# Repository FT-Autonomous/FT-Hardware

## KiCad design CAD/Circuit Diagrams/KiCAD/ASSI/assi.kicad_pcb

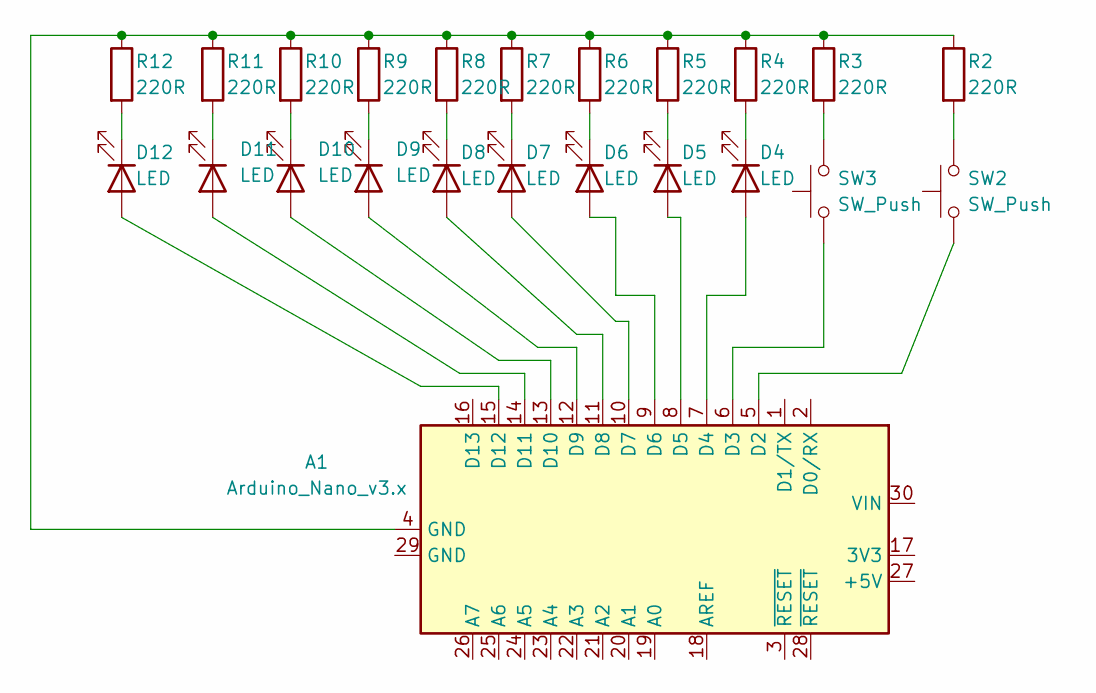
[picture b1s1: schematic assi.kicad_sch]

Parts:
A1: Arduino_Nano_v3.x; Arduino_Nano
D4, D5, D6, D7, D8, D9, D10, D11, D12: LED; LED_D5.0mm
R2, R3, R4, R5, R6, R7, R8, R9, R10, R11, R12: 220R; R_Axial_DIN0207_L6.3mm_D2.5mm_P7.62mm_Horizontal
SW2, SW3: SW_Push; SW_PUSH_6mm

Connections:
unnamed: A1.4 (GND), R2.1, R3.1, R4.1, R5.1, R6.1, R7.1, R8.1, R9.1, R10.1, R11.1, R12.1
unnamed: A1.5 (D2), SW2.1
unnamed: A1.6 (D3), SW3.1
unnamed: A1.7 (D4), D4.2 (A)
unnamed: A1.8 (D5), D5.2 (A)
unnamed: A1.9 (D6), D6.2 (A)
unnamed: A1.10 (D7), D7.2 (A)
unnamed: A1.11 (D8), D8.2 (A)
unnamed: A1.12 (D9), D9.2 (A)
unnamed: A1.13 (D10), D10.2 (A)
unnamed: A1.14 (D11), D11.2 (A)
unnamed: A1.15 (D12), D12.2 (A)
unnamed: D4.1 (K), R4.2
unnamed: D5.1 (K), R5.2
unnamed: D6.1 (K), R6.2
unnamed: D7.1 (K), R7.2
unnamed: D8.1 (K), R8.2
unnamed: D9.1 (K), R9.2
unnamed: D10.1 (K), R10.2
unnamed: D11.1 (K), R11.2
unnamed: D12.1 (K), R12.2
unnamed: R2.2, SW2.2
unnamed: R3.2, SW3.2

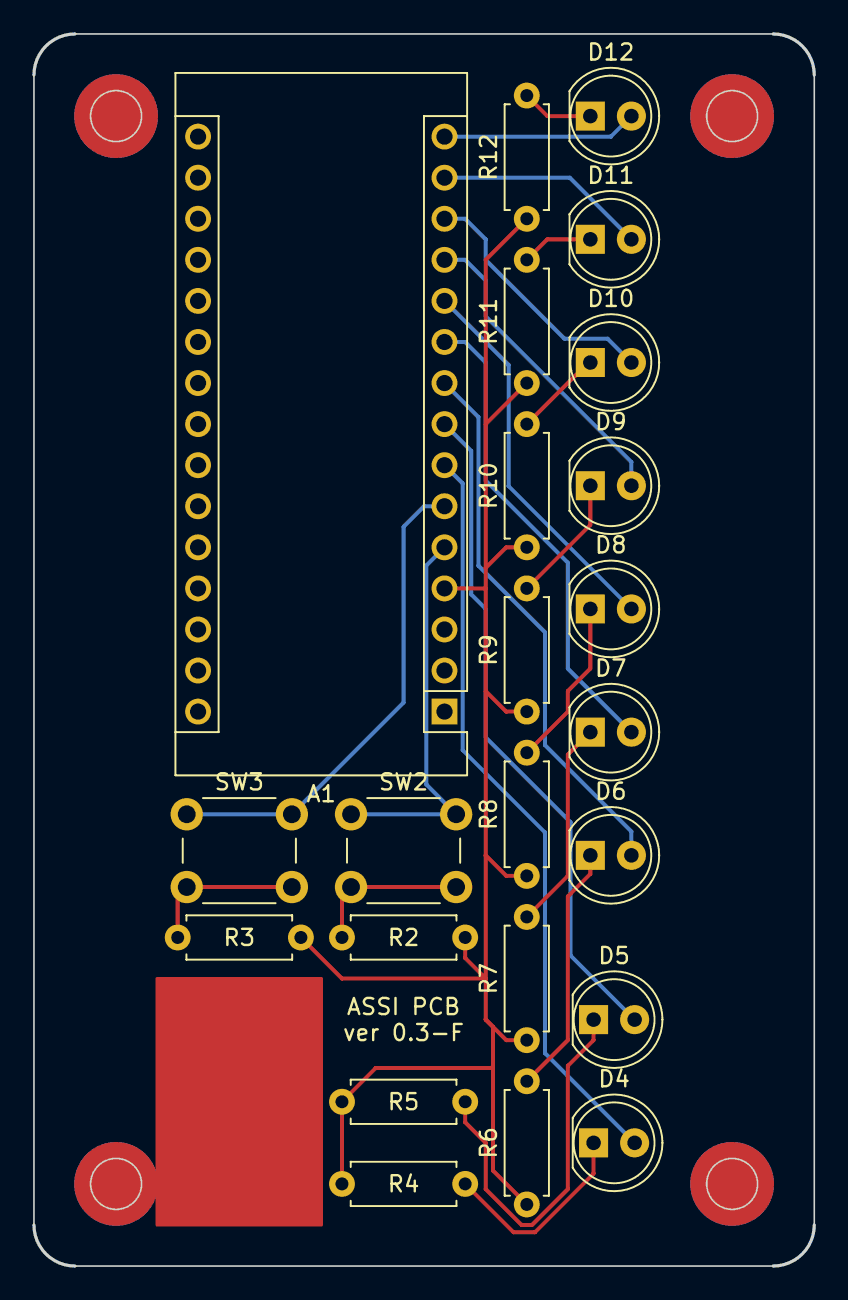
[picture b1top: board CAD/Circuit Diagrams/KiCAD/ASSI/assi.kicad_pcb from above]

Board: 2 copper layers, 48.3 x 76.2 mm, 23 parts (0 on the bottom side), 23 nets.

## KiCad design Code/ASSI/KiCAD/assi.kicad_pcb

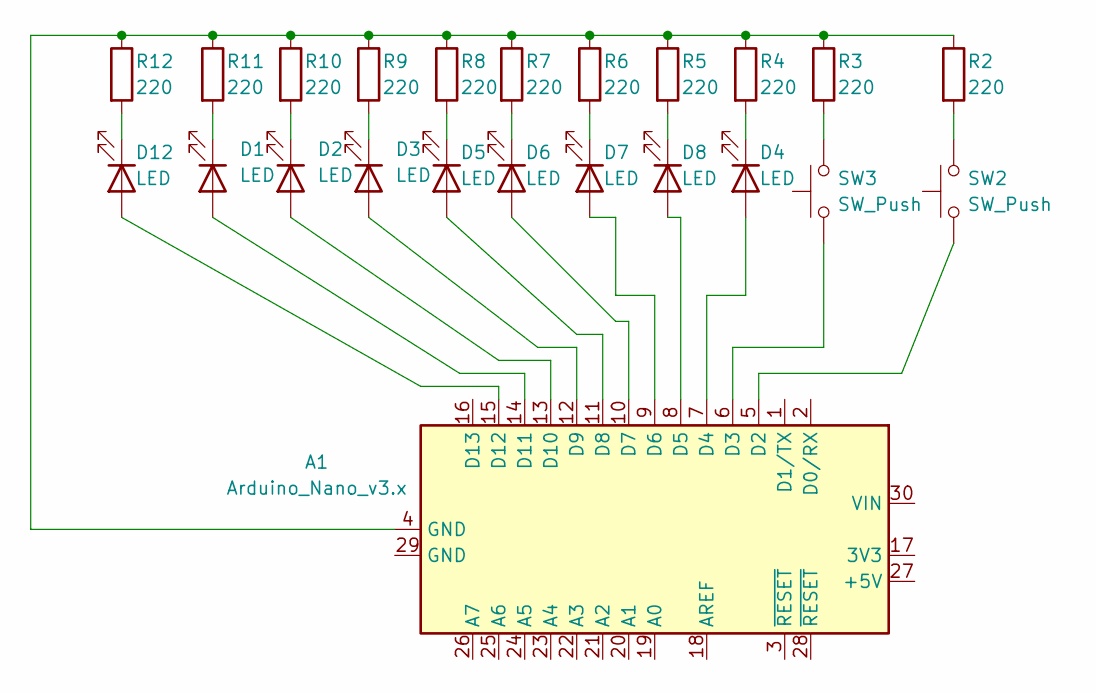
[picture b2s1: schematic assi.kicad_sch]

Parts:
A1: Arduino_Nano_v3.x; Arduino_Nano
D1, D2, D3, D4, D5, D6, D7, D8, D12: LED; LED_D5.0mm
R2, R3, R4, R5, R6, R7, R8, R9, R10, R11, R12: 220; R_Axial_DIN0207_L6.3mm_D2.5mm_P7.62mm_Horizontal
SW2, SW3: SW_Push; SW_PUSH_6mm

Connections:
unnamed: A1.4 (GND), R2.1, R3.1, R4.1, R5.1, R6.1, R7.1, R8.1, R9.1, R10.1, R11.1, R12.1
unnamed: A1.5 (D2), SW2.1
unnamed: A1.6 (D3), SW3.1
unnamed: A1.7 (D4), D4.2 (A)
unnamed: A1.8 (D5), D8.2 (A)
unnamed: A1.9 (D6), D7.2 (A)
unnamed: A1.10 (D7), D6.2 (A)
unnamed: A1.11 (D8), D5.2 (A)
unnamed: A1.12 (D9), D3.2 (A)
unnamed: A1.13 (D10), D2.2 (A)
unnamed: A1.14 (D11), D1.2 (A)
unnamed: A1.15 (D12), D12.2 (A)
unnamed: D1.1 (K), R11.2
unnamed: D2.1 (K), R10.2
unnamed: D3.1 (K), R9.2
unnamed: D4.1 (K), R4.2
unnamed: D5.1 (K), R8.2
unnamed: D6.1 (K), R7.2
unnamed: D7.1 (K), R6.2
unnamed: D8.1 (K), R5.2
unnamed: D12.1 (K), R12.2
unnamed: R2.2, SW2.2
unnamed: R3.2, SW3.2

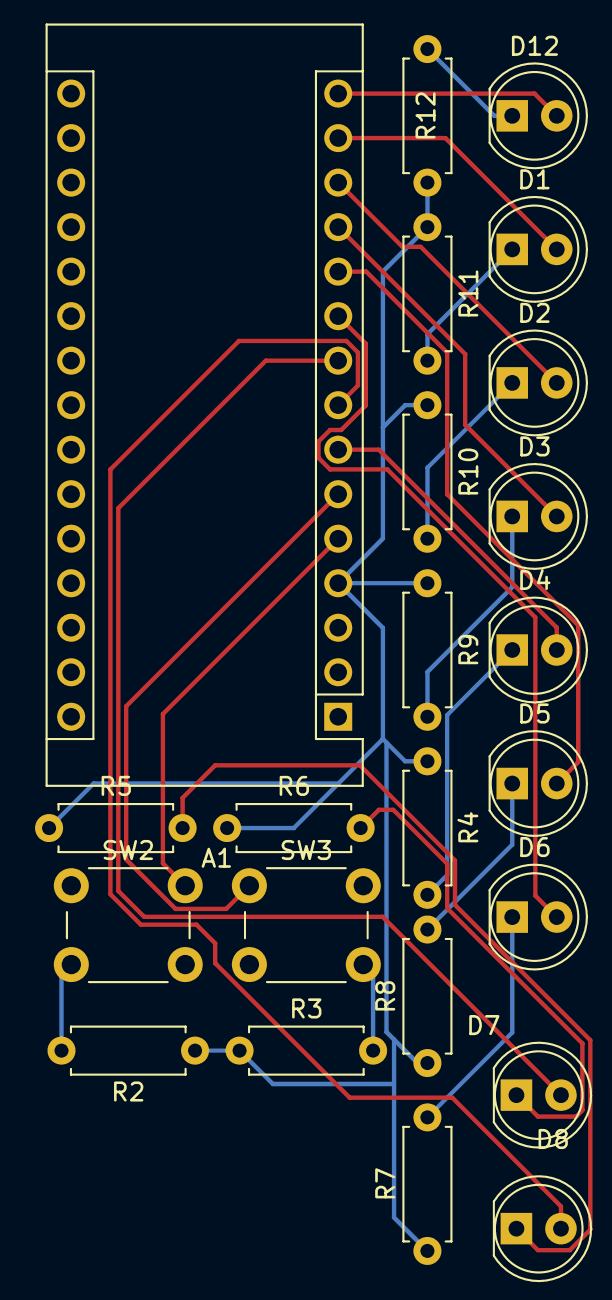
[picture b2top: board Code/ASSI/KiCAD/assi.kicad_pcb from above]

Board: 2 copper layers, 23 parts (0 on the bottom side), 23 nets.

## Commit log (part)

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2025-01-27 Added design todo
2025-01-27 Uploaded CAD Files
2025-02-10 added test file
2025-02-10 new removed
2025-02-10 removed test file ;(
2025-02-24 Added 23/24 Arduino Code
2025-02-24 added encoder adaptor CAD file
2025-03-10 Rigby ASSI half working
2025-03-19 working dual blink mission select
2025-03-24 ASSI and mission select blink working
2025-03-24 finished ASSI state machine
2025-03-24 Encoder mount
2025-03-27 steering mount vf
2025-03-31 wheel holder added
2025-04-05 Commented and fixed decode function
2025-04-05 Changed the decode function to use less complicated, bitwise operations
2025-04-05 added comments
2025-05-23 Encoder code, still working on it so its meh
2025-05-23 Added the pot basic code for steering angle, work in progress
2025-05-26 Updated Encoder code with PID, still working on it
2025-05-26 A PID has been added, just needs a tiny bit of tuning
2025-06-10 added reference comments
2025-06-16 Finished ASSI functionailty pog
2025-06-20 Send Serial from arduino to linux (i use arch btw)
2025-07-10 very basic (but functional) steering code
2025-10-20 Removed test file
2025-10-23 Actuator Test code
2025-10-30 Updated Debug comments to be more clear
2025-10-30 Made a copy of the missionSelect Programme that will complie more easily on ahmeds machine
2025-11-03 Added sendMode functionality to missionSelect(s)
2025-11-03 Sending to python works
2025-11-03 Updated TODO comment
2025-11-05 Decluttered and Reorganised the Git
2025-11-05 removed old files (have been moved)
2025-11-11 Potentiometer mount and connection added
2025-11-13 working python to arduino bridge, need to make some tweaks
2025-11-13 Small clean up, need to tweak a couple things, it works but not fully ready yet
2025-11-13 Improved steering code, work in progress
2025-11-20 Updated steering
2025-11-20 Added test file :)
2025-11-20 removed test file (because Josh is no fun) D:
2025-11-22 Added all previous WIP Lunchy versions
2025-11-22 added modem files (both modem mockup and new casing)
2025-11-22 Added STL for the new camera for this year (the Zed 2i)
2025-11-24 Added updated modem mount (but it's still slightly off D:)
2025-11-26 Maybe actually the right modem casing right but who knows, I'm sure you'll see another modem commit shortly
2025-11-29 LunchyV5 main body, Prototype Sponsor Tiles, Zed2i Assembly - all added
2025-12-30 Tidying CAD repo (deleting)
2025-12-30 re-added CAD but now it's useable for newbies :D
2026-01-19 diagram added
2026-01-19 Added draw.io circuit diagram
2026-01-21 Added LunchyV6 (WIP)
2026-01-25 Added Modem Use Documentation (modem 101 for dummies), LunchyV6 updates, and Sponsor Tile test
2026-01-29 Adding LunchyV7 WIP
2026-01-29 Adding complete Rigby electrical system diagram (WIP)
2026-01-30 LunchyV7 Basically Complete Version :0
2026-02-01 Adding potential Zed2i Mount (needed positioning for Lunchy to confirm placement)
2026-02-02 Added Encoder Mount with inserts, also some Lunchy stuff
2026-02-05 Multi-character serial is real
2026-02-05 Uses multi-char serial to get rid of blocking code from encoder code
2026-02-06 Semi final steering code, some small changes and it will work
2026-02-08 Electrical diagram promoted from WIP
2026-02-08 Wokwi diagram that may or may not be useful in getting the steering to work (I lowkey kinda forget how the motor microcontroler works)
2026-02-08 Makes non-blocking multichar serial with newline and not needing < and > for encoder
2026-02-10 LunchyV8, BrainyV2, Sponsor Logo section added with FT logo (100x100x1)
2026-02-11 Added BrainyV3, updated Lunchy to M6 and fattened basey for screws
2026-02-12 new rotary encoder mount
2026-02-12 Adds the ASSI PCB/Schema from KiCAD and add a .gitignore to parse out KiCAD's temp files
2026-02-13 Added printable A1 versions of encoder to wheel connection, maybe other minor updates to Brainy/Lunchy
2026-02-13 Small ASSI PCB fix
2026-02-15 added test sponsor plate and sliced lunchy
2026-02-16 This is the working steering code, at last we made it :)
2026-02-16 ASSI PCB mountable
2026-02-17 I was told my serial changes may have broken something. Upon reviewing the code I do not belive that to be the case but I have put the function that is slightly less likely to break everything in FT-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
2026-02-26 maybe full steering code with like 2 missing angles
2026-02-27 Non working code allieations has been beaten
2026-02-27 Refactor: functions are good
2026-02-27 1 2 skip a few added a version of the actuator code that interfaces with a custom processing GUI for more optimised testing
2026-02-27 Added the processing test GUI for controlling the actuator
2026-02-27 Removed a call we seemed to be making unessicaraly, set pot pin to the right one, and improved comments
2026-03-01 Creates a new library, FTSerial, so we stop reinventing the wheel and updates Conor's steering code with it. TODO: Hardware code docs so people know this exists and is useful
2026-03-01 Whoops forgot this one
2026-03-01 Reverting gain change so we don't break anything (turn back up for faster steering once we are happy)
2026-03-09 Ahmed version of the code
2026-03-12 Cupholders and stuff
2026-03-12 More cupholders
2026-03-16 Fully working steering code
2026-03-17 multiple updates, might break git - fingers crossed it doesn't - also first Switchy addition
2026-03-19 this took 3 houres
2026-03-20 Adding hopefully completed LunchyV8 (THE Lunchy) CAD and Drawing
2026-03-20 Another one kind done
2026-03-23 Completed SwitchSr added woo, idk what else but something
2026-03-23 firebeetle serial testing
2026-03-23 added arming sequence
    skibidi toilet tung tung tung sahur
2026-03-24 Tested ESP32 with FTSerial. Just make sure FTSerial.cpp and FTSerial.h show when in Arduino
2026-03-27 fixed some edge cases and improved the commenting
2026-03-28 2026 Rough BasePlate for Comp ready, reworked Mount folder to be more usable going forward (we still need to move Platey to Rigby fodler but I think ppl are working out of it right now, so will do in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
2026-03-28 Big changes to Zeddy (Zed2i Holder). Now clears height requirement while attachign to Lunchy, slightly shorter stalk.
2026-03-29 Finalized Mount CAD for 2026 FSAI-DDT Competition + DDT car model - subject to everyone else being happy with it. Includes reworked base plate (2026), Zeddy, SwitchyJr + new Clampy for SwitchyJr to a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
2026-03-29 Finalized DDT Mount with necessary changes made, saved as STEP as per comp requirements, also as solidworks pack and go - located at CAD\Comp resources\ Formula Trinity Additional CAD and Compute Sub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
2026-03-29 Added document detailing Hardware work for CAD submission, realized its missing clearance pictures so will add in morning, also rotated SwitchySr. SwitchyJr flipped has voltage converter screws the w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
2026-03-30 First version of vibrator (rocky) - for ADS/AI testing
2026-04-01 FTSerial can into firebeetle?
2026-04-01 FTSerial ported to Rust, uses a trait instead of Stream& but otherwise same logic
2026-04-01 GetPotentiometerReadings ported to Rust
2026-04-01 FT_Demo_Run ported to Rust
2026-04-01 pot_FT ported to Rust (the Pot-Code one)
2026-04-01 pot_FT with motor control ported to Rust
2026-04-01 Arming sequence ported to Rust
2026-04-01 FT_TOF ported to Rust (ultrasonic + motor control, bugs and all)
2026-04-01 Encoder PID code ported to Rust, kept the custom serial read in there too
2026-04-01 new_steering_code ported to Rust
2026-04-01 WorkingS_PID_Final ported to Rust (it worked!! apparently)
2026-04-01 Last_steerinmg ported to Rust, the one that passed all the tests
2026-04-01 TestSteeringCode ported to Rust, uses FTSerial
2026-04-01 warningLights ported to Rust
2026-04-01 missionSelect (ASSI + Serial combined) ported to Rust, state machine and all
2026-04-01 missionSelectAhmed ported to Rust, the all-in-one version for Ahmed's linux machine
2026-04-01 Simple ActuatorCode ported to Rust
2026-04-01 ASSStateMachine ported to Rust, still a draft/WIP
2026-04-01 ADS Networking helper functions ported to Rust
2026-04-01 MySketch serial proof of concept ported to Rust
2026-04-01 fireBeetle serial test ported to Rust, uses FTSerial
2026-04-01 mainCode stub ported to Rust (still empty)
2026-04-01 mpu6050_min driver ported to Rust, I2C trait instead of TwoWire reference
2026-04-01 si7021_min temperature driver ported to Rust
2026-04-01 MYOSA VibrationLogger ported to Rust, BLE + sensor fusion + the whole lot
2026-04-01 glcdfont data ported to Rust, just a const array
2026-04-01 MYOSA Actuator (PCA9536 I/O expander) ported to Rust
2026-04-01 MYOSA AirQuality (CCS811 gas sensor) ported to Rust
2026-04-01 MYOSA AccelAndGyro (MPU6050) ported to Rust, all 50+ methods
2026-04-01 MYOSA BarometricPressure (BMP280) ported to Rust
2026-04-01 MYOSA Blink example ported to Rust
2026-04-01 2_OLED_demo example ported to Rust
2026-04-01 8_AirQuality_Demo example ported to Rust
2026-04-01 4_BarometricPressure_Demo example ported to Rust
2026-04-01 7_Gesture_Demo example ported to Rust
2026-04-01 5_AccelAndGyro_Demo example ported to Rust
2026-04-01 6_LightProximity_Demo example ported to Rust
2026-04-01 9_Actuator_Demo example ported to Rust
2026-04-01 TempAndHumidity library ported to Rust
2026-04-01 MYOSA wrapper library ported to Rust
2026-04-01 Adafruit_GFX ported to Rust - graphics primitives and all that jazz
2026-04-01 Adafruit_SSD1306 OLED driver ported to Rust
2026-04-01 #2_Experiments examples ported to Rust (MasterCode, BurglarAlarm, GestureControlledLight)
2026-04-01 #3_Wi-Fi examples ported to Rust (ScanNearby, GetTime, ControlPanel)
2026-04-01 OLED wrapper library ported to Rust - 3D cube and all
2026-04-02 Made some assemblies more lightweight so we could get total zipped competition zip below 20mb
2026-04-07 Slight reorganisation of Brainy components to move modem into its folder, also some parts of the new modem mini/SE added
2026-04-07 adding routey SE parts I forgot to add in last push :(
2026-05-07 CAD redo to have Rigby working better and moving Platies over to Rigby part yay, still incomplete but everything better in right place
2026-05-08 Printable Platey (Rigby Brain) Parts Added (the STL's, 3mf, etc for V1
2026-05-12 Add multi serial python script for the firebeetles
2026-05-13 Uses MAC addresses to identify each ESP32
2026-05-14 Makes the MAC addresses actually work
2026-05-19 better cupholders, 3D-prinable
2026-05-19 Adds FT logo footprint library
2026-05-19 Test code for the braking motor, accepts PWM commands and computes current RPM
2026-05-21 More complete Platey model with front steering and potentiometer (thanks Jade), still needs to be scaled down and platforms raised. Motor Controller model added, downloaded from internet.
2026-05-21 Correct Lunchy so it isn't overridden which for some reason my laptop decided to do :(. Will overwrite Rigby, but I'll fix later soz
2026-05-25 Completed Rigby with Lunchy (omg so wow), then a half failed exploded view, drawings added, visualize instance added I think, mock Jetson nano cover but we should not use as it has way too many faces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
2026-06-04 Front exploded tyes of Rigby exploded done, new nubbies finalized - documentation in Hardware Mech channel for now, those are nubby v2 - also printed with a 3mf there for attaching. Steering has been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
2026-06-04 Adds power connector spreadsheet in managment folder
2026-06-04 Revert "Adds power connector spreadsheet in managment folder"
    This reverts commit f2c0c09fea6657efe5c688cf131e826e31b96cae.
2026-06-05 added 1st part of template for actuator movement for Control
2026-06-06 Linear Potentiometer Template
2026-06-06 actuator P controller draft 1
2026-06-06 minor serial changes
2026-06-23 RGB + Button check
2026-06-26 Renamed the 'Rigby' folder to 'Steering'
2026-06-26 Cleaned up the Steering code folder
2026-06-26 Fixed the Readme section
2026-06-26 Cleaning Files
2026-06-26 Moved steering to rigby folder
2026-06-26 Organised the ASSI folder, needs to be refactored
2026-06-29 ASSI Code matches the new hardware
2026-06-30 digitalWrite instead of analog to test level shifters
2026-06-30 more advanced control loop for testing
